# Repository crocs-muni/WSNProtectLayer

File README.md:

WSNProtectLayer
===============

TinyOS layer for configurable protection of message privacy, intrusion detection and key distribution

Design and implementation was supported by project VG20102014031 of Ministry of Interior, Czech Republic
"Experimentální vývoj bezpečnostní softwarové platformy se systémem detekce průniku a režimy ochrany soukromí pro bezdrátové senzorové sítě" (in Czech).

Following people are (were) involved: Vashek Matyas, Petr Svenda, Andriy Stetsko, Jiri Kur, Filip Jurnecka, Martin Stehlik, Tobias Smolka, Dusan Klinec, Roman Zilka, Jaromir Dobias, Vit Bukac, Marcel Gazdik and Lukas Nemec.

##How to get ProtectLayer##
- Fork your own repository (at Github)
- or create local clone of repository (desktop)
- or download all sources in single zip file (Download ZIP)

##What you will get##

**Core components**
- ProtectLayer ... implementation of ProtectLayer middleware with all core functions. Other applications are wired against this implementation
- ProtectLayerConfigurator ... configuration application responsible for storage of cryptographic keys into flash memory during predistribution
- Uploader ... server side Java application communicating with ProtectLayerConfigurator and providing predistributed keys

**Scenario-specific applications**
- PL_BaseStation ... base station node with ProtectLayer middleware 
- PL_BlinkToRadio ... testing application with network communication with ProtectLayer middleware 
- PL_PoliceApp ... application for ordinary nodes inside network. Supports detection of MSNs, emitting still alive packets
- IntruderApp ... application used for special nodes used as mobile beacon reported to BS (MSN, virtual attacker)   

**Hardware extensions**
- Zilog ... application with ability to sample and respond on movement detection sensor Zilog ePir
- rfid ... application with ability to sample and respond on wireless card close to connected RFID reader

**Management and statistics gathering applications** 
- ManagementApp ... set of server-side scripts for batch control of nodes 
- TOSCTP ... application usable for testing CTP routing discover protocol performance
- rssi_csv_to_tossim ... application usable for testing signal propagation and RSSI 
- BlinkNodeIDApp ... testing application without any network communication. Node blinks its own ID

##How to use it##

- Compile and upload Base station node: 
```
  cd /tinyos/PL_BaseStation/src
  make telosb install,14 bsl,/dev/ttyUSB0
  run listener:java net.tinyos.tools.PrintfClient -comm serial@/dev/ttyUSB0:telosb
```
- Wire ProtectLayer instead of AMSend and Receive interfaces
```
  components ProtectLayerC;
  App.Packet -> ProtectLayerC.Packet; 
  App.AMControl -> ProtectLayerC.AMControl;
  App.AMSend -> ProtectLayerC.AMSend;
  App.Receive -> ProtectLayerC.Receive;
```
- Compile and upload Ordinary node with your application (e.g., PL_PoliceApp): 
```
  cd /tinyos/PL_PoliceApp/src
  make telosb install,21 bsl,/dev/ttyUSB1
  run listener:java net.tinyos.tools.PrintfClient -comm serial@/dev/ttyUSB1:telosb
```
- Compile and upload Sniffer for additional network informations (raw packets): 
```
  cd /opt/tinyos-2.1.1/apps/BaseStation
  make telosb install,14 bsl,/dev/ttyUSB2
  run listener: java net.tinyos.tools.Listen -comm serial@/dev/ttyUSB2:telosb
```

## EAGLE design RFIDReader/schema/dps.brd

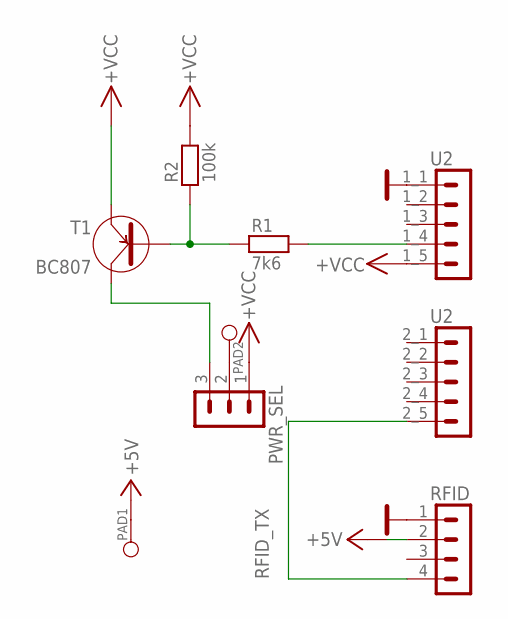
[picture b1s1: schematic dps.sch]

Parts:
PAD1: +; PAD_1
PAD2: -; PAD_1
PWR_SEL: S1G3_JUMP; S1G3_JUM
R1: 7k6; 1206
R2: 100k; 1206
RFID: S1G4_JUMP; S1G4_JUM
T1: BC807; SOT-23
U2: S2G5_JUMP; S2G5_JUM

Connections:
+5V: PAD1.1, RFID.2
GND: RFID.1, U2.1_1 (1)
unnamed: PAD2.1, PWR_SEL.2
unnamed: R1.1, R2.1, T1.1 (B)
unnamed: R1.2, U2.1_4 (4)
unnamed: PWR_SEL.3, T1.3 (C)
RFID_TX: RFID.4, U2.2_5 (5)
VCC: PWR_SEL.1, R2.2, T1.2 (E), U2.1_5 (5)

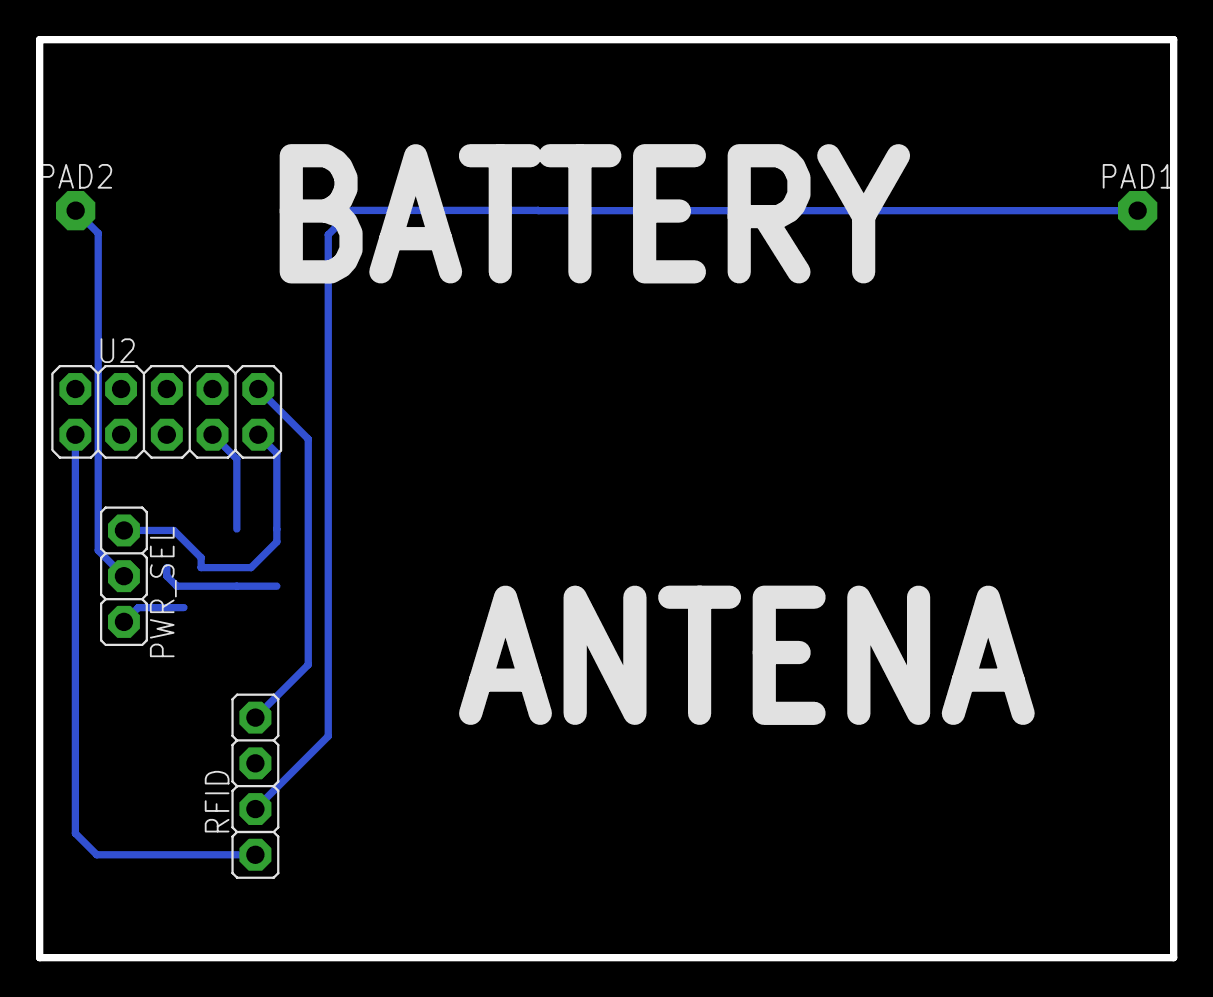
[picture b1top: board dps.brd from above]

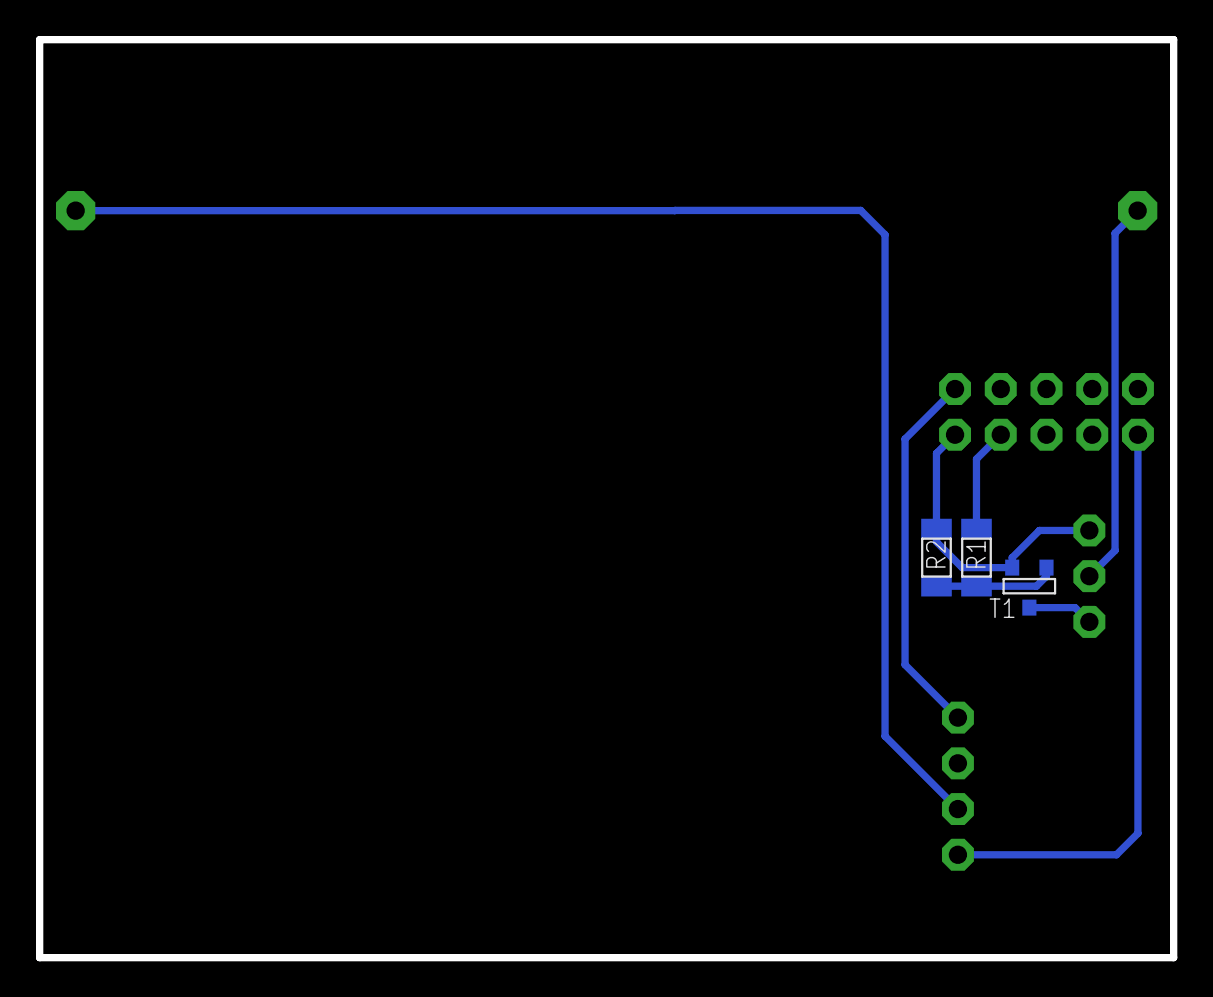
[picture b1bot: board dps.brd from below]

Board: 2 copper layers, 63.0 x 51.0 mm, 8 parts (3 on the bottom side), 8 nets.

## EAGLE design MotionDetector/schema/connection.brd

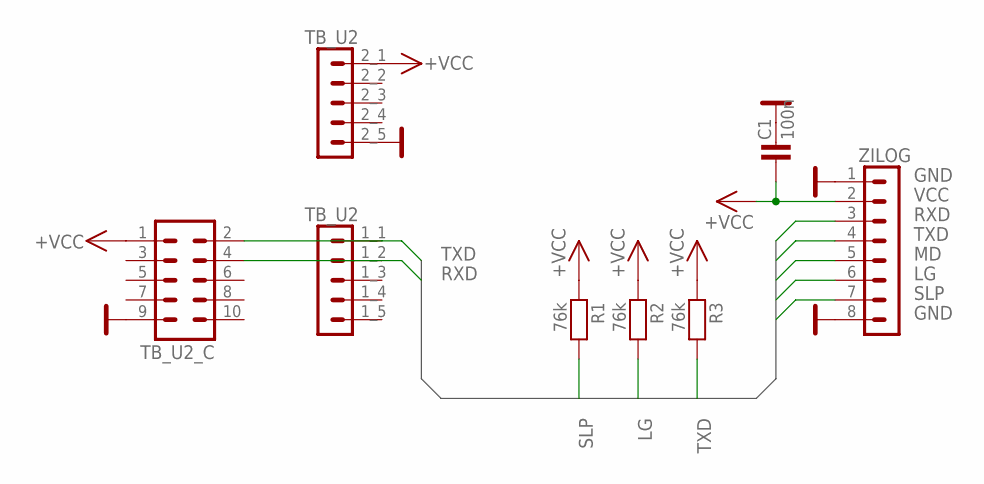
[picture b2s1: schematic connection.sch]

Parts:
C1: 100n; 1206
R1, R2, R3: 76k; 1206
TB_U2: S2G5_JUMP; S2G5_JUM
TB_U2_C: MLW10; MLW10G
ZILOG: S1G8_JUMP; S1G8_JUM

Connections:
GND: C1.2, TB_U2.2_5 (5), TB_U2_C.9, ZILOG.1, ZILOG.8
LG: R2.2, ZILOG.6
MD: ZILOG.5
RXD: TB_U2.1_2 (2), TB_U2_C.4, ZILOG.3
SLP: R1.2, ZILOG.7
TXD: R3.2, TB_U2.1_1 (1), TB_U2_C.2, ZILOG.4
VCC: C1.1, R1.1, R2.1, R3.1, TB_U2.2_1 (1), TB_U2_C.1, ZILOG.2

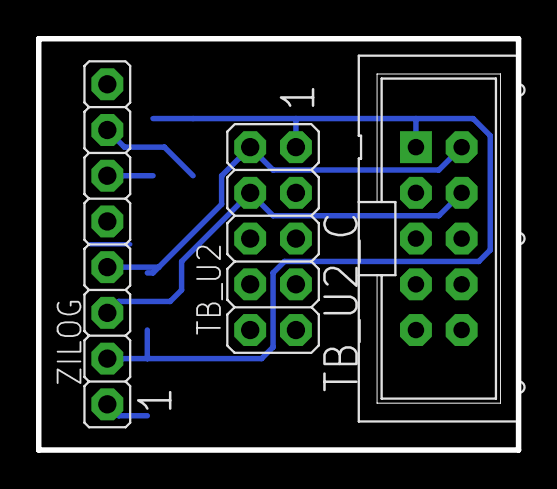
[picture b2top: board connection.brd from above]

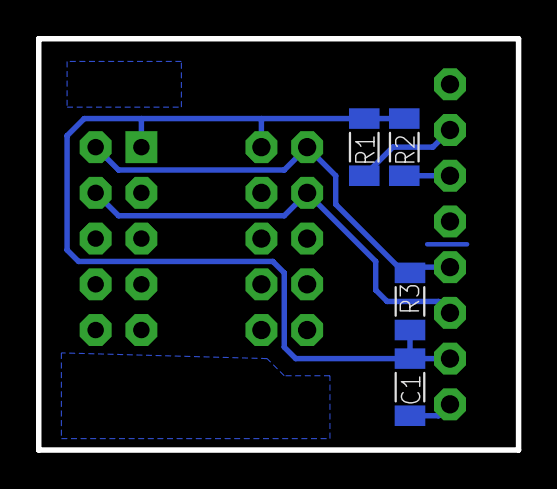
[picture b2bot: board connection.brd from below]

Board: 2 copper layers, 26.7 x 22.9 mm, 7 parts (4 on the bottom side), 6 nets.

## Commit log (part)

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2013-08-14 KeyDistribP modification component changed to derive key as xor value of challenges
2013-08-14 KeyDistrib version number changed
2013-08-23 KeyDistrib, Crypto changed KeyDistrib working as xor of challenge values Crypto added random generation
2013-10-24 new file: Daemon/WSNManager/App/ArrayHash.ctxt new file: Daemon/WSNManager/App/ArrayHash.java new file: Daemon/WSNManager/App/BaseController.ctxt new file: Daemon/WSNManager/App/BaseController.java n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
2013-10-25 new file: App/Service.java deleted: ConfigException.ctxt deleted: ConfigLoader.ctxt deleted: DbDriver/Database.ctxt deleted: DbDriver/DatabaseInterface.ctxt deleted: DbDriver/DbException.ctxt deleted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
2013-10-25 modified: App/ArrayHash.java modified: App/BaseController.ctxt modified: App/BaseController.java modified: App/Context.ctxt modified: App/Context.java modified: DbDriver/Database.java modified: Main.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
2013-11-14 removed files from tracking
2013-11-14 removed changes introduced from branch KeyPredistrib
2014-01-07 skipjack added
2014-01-07 additional files for skipjack
2014-01-13 todos for next implementation phase
2014-01-13 AES connection to crypto
2014-01-13 added AES to encryptBufferB
2014-01-13 AES counter mode for RAW crypto implemented
2014-01-13 Added dispatcher and related components
2014-01-13 crypto Raw files added content moved from crypto
2014-01-13 crypto and cryptoRaw headers modified
2014-01-14 new convinience crypto header created modified keyDistrib header for key retrieval
2014-01-14 AES define changed to use else notation
2014-01-14 convinience crypto implementation started
2014-01-14 crypto headers changed to protect/unprotect from encrypt/decrypt
2014-01-14 mac functionality added
2014-01-14 key derivation added predistributed key format specified
2014-01-15 dodelany dalsi zpravy a spoustu dalsiho..
2014-01-15 doplneny zpravy, uprava dalsich casti kodu, pridany chybejici soubory
2014-01-16 predistributed key format changed to fit network type
2014-01-16 few bugs removed from crypto and cryptoRaw
2014-01-16 counter overflow check
2014-01-16 initial configuration app commit
2014-01-16 changed discover keys command to blocking version
2014-01-17 added initialization tree to dispatcher, but only part of it
2014-01-17 hash function added
2014-01-17 hash header changed to take nodeID instead of key couter space increased to uint_32
2014-01-17 get key to BS implemented
2014-01-17 synchronization
2014-01-17 synchronization and bugs removal, now can be compiled
2014-01-18 added SaveSataPart messgae. This message allows save combinedData structure by parts.
2014-01-20 global variables reduced
2014-01-20 Removed or renamed unnecesary components, added inits
2014-01-20 hash headers and functionality modified
2014-01-20 added IDS forwarder
2014-01-20 enhanced IDS forwarder
2014-01-21 half hash header added cryptoRaw test implemented
2014-01-21 hash data half header added
2014-01-21 half hash implemented
2014-01-21 fixed wrong parameters to PrintfDbg
2014-01-22 sigmature verify bugs removed
2014-01-22 commit message
2014-01-23 printf working
2014-01-23 KeyDistrib and Crypto self tests
2014-01-23 dispatcher & fixed shared data implementation
2014-01-23 IDS implemetnation almost finished
2014-01-23 compilable version
2014-01-23 Dispatcher wired into AMControl.start().
2014-01-23 Dispatcher interface added.
2014-01-23 Fixed printf messages.
2014-01-23 printf buffer size increased
2014-01-24 printDbg format string
2014-01-24 Shared data debug info added
2014-01-24 Changes in IDS, IDSForwarder. Sending IDS alerts.
2014-01-24 Changes in printf in PoliceApp, printf buffer in Makefila
2014-01-25 Small change in IDS buffer
2014-01-27 printf contition to TOS_NODE_ID added
2014-01-27 printfflush added to all printf calls
2014-01-28 printf output from all nodes, not dependant on TOS_NODE_ID
2014-01-28 Printf shell scripts fixes, reset nodes before start option
2014-01-28 shell scripts for multiple PrintfClients
2014-01-29 key uploader (tinyos,java)
2014-01-29 compile warnings from ProtectLayerConfigurator removed
2014-01-30 BlinkNodeID application for visual verification of the node ID
2014-01-30 printf removed from SoftwareInit event handler.
    * printf cannot be called from SoftwareInit (probably due to some race conditions, probably a serial port is not opened that time)
2014-01-30 runPrintf.sh: Kill listening PrintfClients before starting a new one
2014-01-31 fixed bug in shared data - invalid memory access, no printfflush
2014-01-31 Intruder, MSN, key upload, key download
2014-01-31 Blink2radio - sending no messages, only radio init. Printfbuffer=1024
2014-01-31 forwarder uses tasks for sending
2014-01-31 Dispatcher & privacy init refactored to split phase. Printf works. Retx timer
    * Some nodes are still freezing after some time - I dont know why yet...
2014-01-31 no freezing, unprotect buffer commented
2014-01-31 fix bug in CryptoP - subtracting from a pointer.
2014-01-31 Some arguments sanity checks in CryptoP in order to avoid app crash.
    * TODO: add sanity checks to all methods.
2014-01-31 CryptoP bug fixed with iteration over block
2014-02-01 first draft for new logging
2014-02-01 Refactoring, demo of the new logging in PrivacyP.
2014-02-01 Blink blinks2radio
2014-02-01 ability to redefine log level in separate components
2014-02-03 MSN detection
2014-02-03 fixes in IDS, PrivacyP no copy for IDS
2014-02-03 Crypto bugs fixed, headers slightly changed signature update function added short hash changed from uint64 to uint32
2014-02-03 mac functions changed
2014-02-03 privacyP: msgRecv implemented (w.r.t. PL), added phantom jumps field to SPheader, code cleaning.
    * message receive respects current privacy level, code structure refactored.
    * removed garbage code fragments.
2014-02-03 Crypto bugs fixed part II.
2014-02-03 privacyP: code refactoring of msg send
2014-02-04 Crypto bugs fixed, part III.
2014-02-04 counter synchronization implemented
2014-02-04 hop by hop encryption define
2014-02-04 signature functions modified
2014-02-04 PrivacyLevel component finished. CryptoP - fixed verify signature. privMsg changed.
    * PrivacyLevel component works as expected.
    - Rebroadcasts new valid messages.
    - Manages global counter (newly added!).
    - Logic similar to ForwarderP.
    - Using PLInit to load SharedData (for global counter).
    * CryptoP - fixed problem with verify signature, memcompare is performed only one (with cons. with Jirka).
2014-02-04 Conditional compilation for hop-by-hop encryption (after cons. with Jirka).
    * Hop-by-hop protection would require counter sync (should be implemented), but is comp. overhead and IDS would have troubles with this.
    * Code cleanup, some branches not needed.
2014-02-04 IDS wants message sent by APP (parent should forward)
2014-02-04 TOS CTP imported from my repo
2014-02-04 CTP engine added to the RouteComponent
    * Conditional compilation (define USE_CTP). Used only to determine random neighbor.
    * Is started on init, runs a few seconds (60), sends dummy messages in order to establish valid CTP tree.
    Then if parent is still not found, CTP recompute & triggerUpdate is called with message send. If next 60s CTP is turned off (it is possible no valid parent exists).
2014-02-04 Conditional compilation for base station.
2014-02-05 crypto documentation and bugs fixed
2014-02-05 compute signatures function added to Crypto
2014-02-06 base station draft
2014-02-06 MagicPacket interface
2014-02-06 fixed typo in log
2014-02-06 RouteP: CTP init refactored
2014-02-06 Basestation - change of PL with Led signals, button
2014-02-06 crypto signature functions updated
2014-02-06 signature functions updated documentation
2014-02-06 Crypto signature bug removed
2014-02-06 BaseStation should forward
2014-02-06 globals: compile constants
2014-02-06 BS computes signature
2014-02-06 predistributed values of signatures computation
2014-02-06 printf on demand, BS fixed button press
2014-02-06 ACCEPT_ALL_SIGNATURES macro
2014-02-06 quick CTP init define macro, use CTP by default
2014-02-06 fix bug in randomNeigh seleciton, printf->pl_log
2014-02-06 shared data -> pl_log
2014-02-06 pl_printf -> pl_log_x: ForwarderP, KeyDristribP
2014-02-06 fixed multiple bugs with return of pointer PL_key_t* -> PL_key_t*
2014-02-06 SKIP_MAGIC_PACKET macro
2014-02-06 Changes in IDS alerts sending and printfs in IDS
2014-02-06 PrivacyLevel: fixed privLvlChange re-broadcast.
2014-02-06 fixed confusing log message (for Martin to be happy :D)
2014-02-07 Police app init refactored. Using tasks for sending.
2014-02-07 small tuning of the CTP start.
2014-02-07 - fixed bugs mainly in Crypto: * wrong parameters order in AES.encrypt, * hash key changed and never returned to initial value
2014-02-07 - fixed problem with non-supplied key for derivation
2014-02-07 crypto self test called and shows result with leds
2014-02-07 minor updates in Intruder app
2014-02-07 fex fixes in route comp. Copy plaintext to SPheader disabled temporarily
2014-02-07 dump ctp neighbors in blink to radio
2014-02-07 Small changes in IDS.
2014-02-07 40 -> 22 fixed routing
2014-02-07 pre-Mirov version
2014-02-11 Buffered message forwarder.
    * Taken from CTPForwardingEngineP.
    * No connection to Route - is handled in Privacy component.
    * No ACKs since send is done on broadcast (thus no link estimator and sim. stuff).
    * NOT TESTED, without compilation errors / warnings.
2014-03-24 using CTP parents and neighbors now, deleted few obsolete components, resolved/deleted few minor TODOs
2014-03-26 ctp used and tested
2014-03-26 crypto mac fixed bugs
2014-03-28 Just give me my repository access!!!!
2014-03-28 EEPROM access rewritten
2014-03-28 SharedDataP save state to eeprom added Reading keys from eeprom
2014-03-31 Added waiting for long operations in dispatcher
2014-03-31 State is saved and loaded in EEPROM.
2014-03-31 signature tests
2014-04-01 dispatcher reworked, selected logs disabled because of memmory restrictions split phase operation inside dispatcher transformed into blocking via state finished function
2014-04-01 Dispatcher explaining comments added
2014-04-02 Added stateChanged() event for BaseStation.
2014-04-02 Corrected names of volumes in EEPROM for BaseStationApp.
2014-04-02 I don't even know and I don't care.
2014-04-02 Umm.. state automaton
2014-04-02 unused variables removed
2014-04-03 dispatcher fixed redundant break;
2014-04-03 Few BS fixes, app works (without signature verification).
2014-04-03 Define BS Node ID in header files.
2014-04-03 SKIP_EEPROM_RESTORE define constant added.
2014-04-10 rfid & zilog ePir application added
2014-04-15 usage added to readme
2014-04-17 removupdated movement, rfid
2014-04-23 Modified comments, remove some TODOs, version changed to 1.0
2014-04-24 Finished TODOs
2014-04-24 Erased some legacy TODOs.
2014-04-24 added multipath delivery of IDS alert messages
2014-04-28 NesDocs updated
2014-04-29 In the process of reading information for simulation presentation tion.
2014-04-29 Changed all pl_printf to pl_log_x.
2014-04-30 Removed sim output from IDS, adjusted in IDSForwarder.
2014-04-30 Adding flooding IDSAlert at the first hop caused problems in computation of the hash for the IDS buffer. This problem has to be solved either in such a way that IDS alert will not be monitored (dropp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
2014-04-30 Minor change in IDSalert logging in case we would use it.
2014-04-30 Nesdoc updated
2014-05-05 warnings removed
2014-05-05 Uncommented IDS
2014-05-05 updated defines and related warnings
2014-05-05 Added TimeStampPrintfClient
2014-05-05 Fixed bad base station define in PoliceApp.h
2014-05-06 Added scripts for running the TimeStampPrintfClient
2014-05-06 Fixeed various little bugs and uncommented some simulation output.
2014-05-07 Retransmission
2014-05-12 license updated to BSD 2-Clause License

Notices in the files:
parts and their libraries:
Copyright (C) PaJa 2011
Copyright (C) PaJa 2001-2011
Copyright (C) PaJa 2001-2010
